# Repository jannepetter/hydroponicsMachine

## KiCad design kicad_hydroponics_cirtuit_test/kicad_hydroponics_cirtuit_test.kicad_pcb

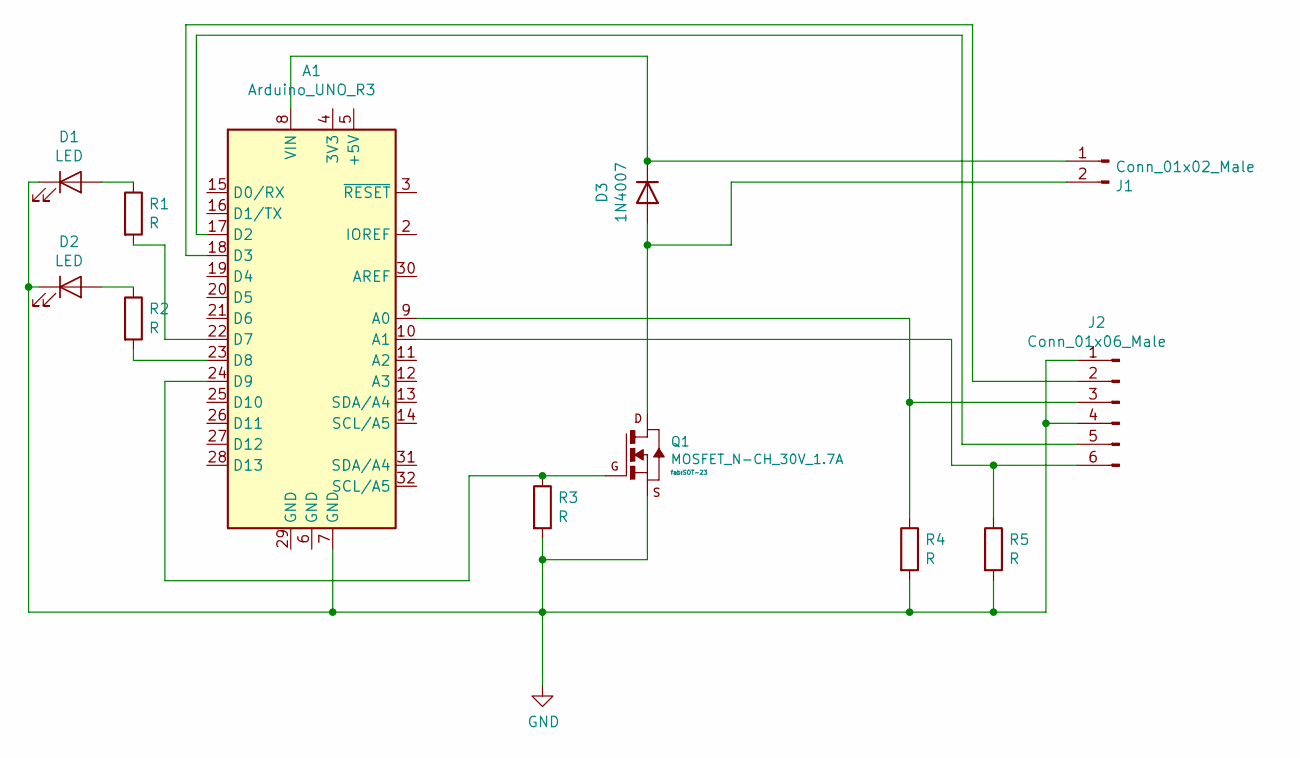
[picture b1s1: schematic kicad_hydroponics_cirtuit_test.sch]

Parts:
A1: Arduino_UNO_R3; Arduino_UNO_R3_WithMountingHoles
D1, D2: LED; LED_1206
D3: 1N4007; D_DO-41_SOD81_P10.16mm_Horizontal
J1: Conn_01x02_Male; Header_SMD_01x02_P2.54mm_Horizontal_Male
J2: Conn_01x06_Male; Header_SMD_01x06_P2.54mm_Horizontal_Male
Q1: MOSFET_N-CH_30V_1.7A; SOT-23
R1, R2, R3, R4, R5: R; R_1206

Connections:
GND: A1.7 (GND), D1.1 (K), D2.1 (K), J2.1, J2.4, Q1.2 (S), R3.2, R4.2, R5.2
unnamed: A1.8 (VIN), D3.1 (K), J1.1
unnamed: A1.9 (A0), J2.3, R4.1
unnamed: A1.10 (A1), J2.6, R5.1
unnamed: A1.17 (D2), J2.5
unnamed: A1.18 (D3), J2.2
unnamed: A1.22 (D7), R1.2
unnamed: A1.23 (D8), R2.2
unnamed: A1.24 (D9), Q1.1 (G), R3.1
unnamed: D1.2 (A), R1.1
unnamed: D2.2 (A), R2.1
unnamed: D3.2 (A), J1.2, Q1.3 (D)

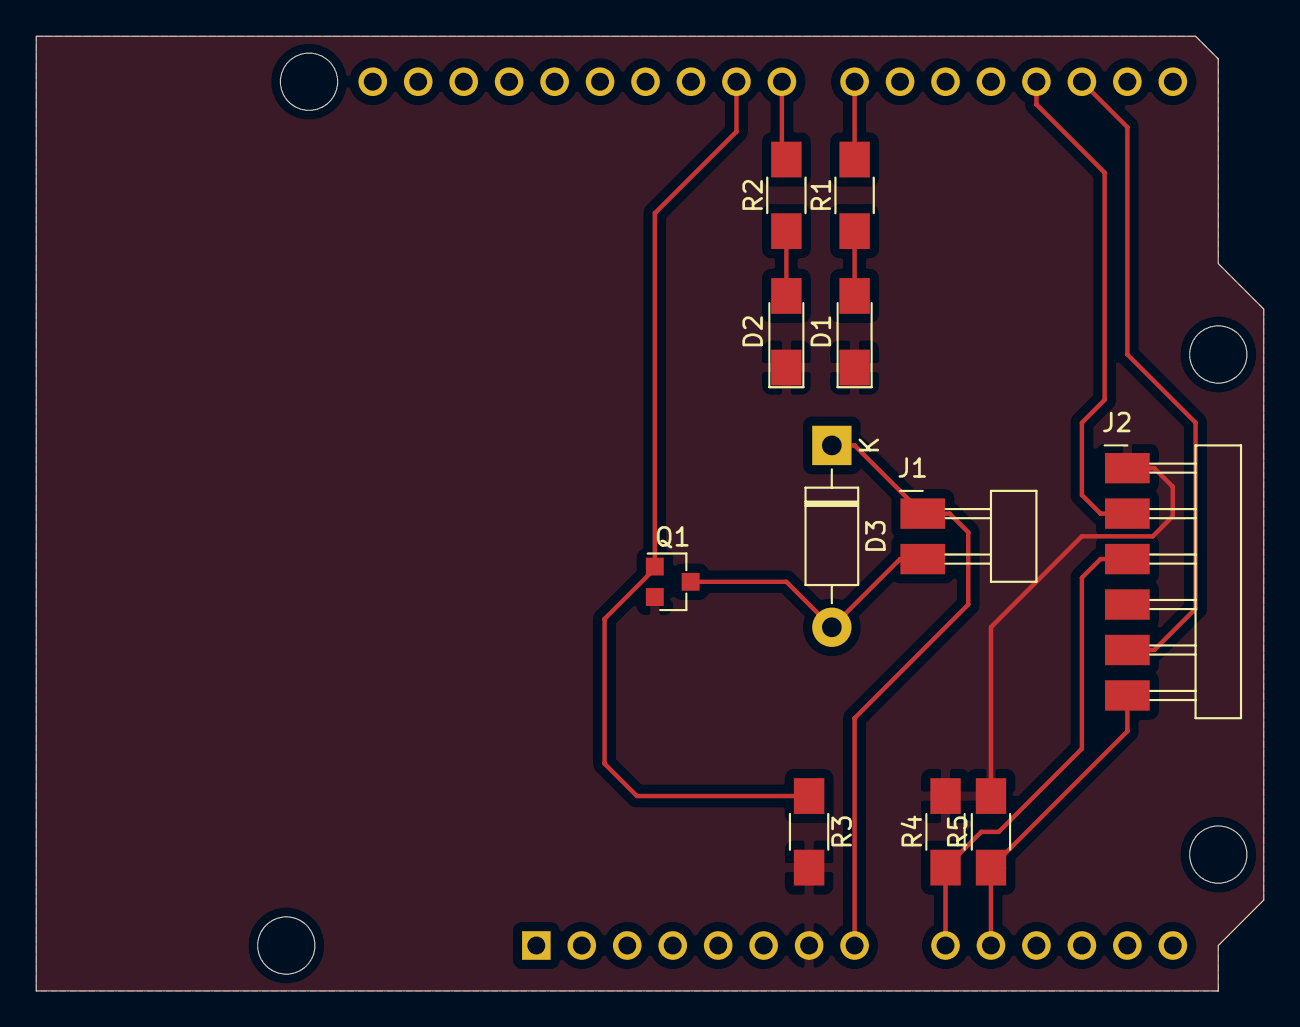
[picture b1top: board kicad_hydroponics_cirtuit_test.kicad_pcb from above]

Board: 2 copper layers, 68.6 x 53.3 mm, 12 parts (1 on the bottom side), 12 nets.

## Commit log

2021-03-29 2d sketches
2021-03-30 Fusion 360 3D sketch for water pump
2021-03-30 mods to tanks
2021-03-30 rounded corners
2021-03-31 Motor cover design update to enable assembly
2021-04-06 Optional water inlet to mount pump to bottom.
2021-04-07 Fix pump cover as component Add components stl files
2021-04-11 gravel box added
2021-04-20 Uploaded KiCad files that need to be improved
2021-04-21 Updated to use SMD components except diode 1N4007 is through hole. Water level sensor powering from Arduino digital pins to prevent sensor electrochemical corrosion
2021-04-22 arduino box added
2021-04-25 Uploaded the code file for Arduino
2021-04-26 Add gerber files
2021-04-28 modified and added variables, made the code clearer and added max on-time for the pump
2021-04-28 yellow light fix
2021-04-29 threshold changes
2021-05-05 added presentations
